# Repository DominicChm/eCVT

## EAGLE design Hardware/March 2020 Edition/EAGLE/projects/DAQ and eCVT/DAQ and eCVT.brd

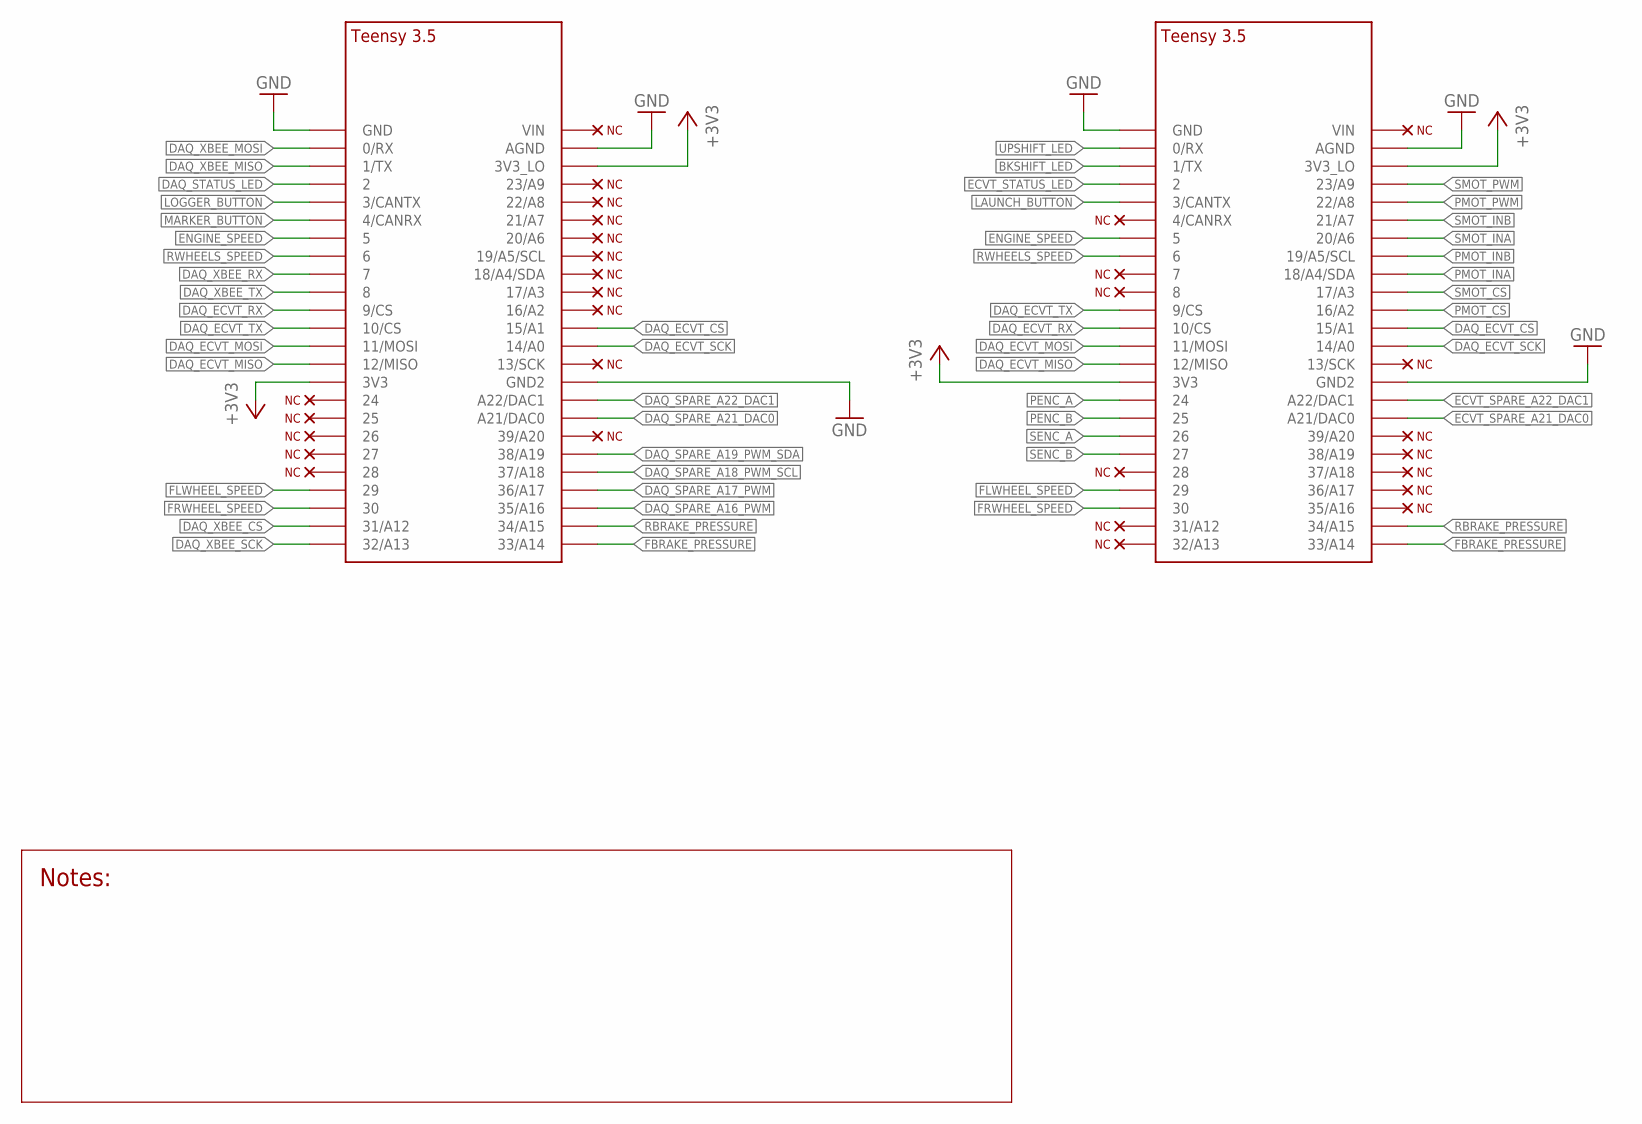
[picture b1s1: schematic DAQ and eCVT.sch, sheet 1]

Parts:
U$31, U$33: TEENSY_3.5_BAJA

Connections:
+3V3: U$31.3V3, U$31.3V3_LO, U$33.3V3, U$33.3V3_LO; also elsewhere on the board
BKSHIFT_LED: U$33.1/TX; also elsewhere on the board
DAQ_ECVT_CS: U$31.15/A1, U$33.15/A1
DAQ_ECVT_MISO: U$31.12/MISO, U$33.12/MISO
DAQ_ECVT_MOSI: U$31.11/MOSI, U$33.11/MOSI
DAQ_ECVT_RX: U$31.9/CS, U$33.10/CS
DAQ_ECVT_SCK: U$31.14/A0, U$33.14/A0
DAQ_ECVT_TX: U$31.10/CS, U$33.9/CS
DAQ_SPARE_A16_PWM: U$31.35/A16; also elsewhere on the board
DAQ_SPARE_A17_PWM: U$31.36/A17; also elsewhere on the board
DAQ_SPARE_A18_PWM_SCL: U$31.37/A18; also elsewhere on the board
DAQ_SPARE_A19_PWM_SDA: U$31.38/A19; also elsewhere on the board
DAQ_SPARE_A21_DAC0: U$31.21/DAC0 (A21/DAC0); also elsewhere on the board
DAQ_SPARE_A22_DAC1: U$31.A22/DAC1; also elsewhere on the board
DAQ_STATUS_LED: U$31.2; also elsewhere on the board
DAQ_XBEE_CS: U$31.31/A12; also elsewhere on the board
DAQ_XBEE_MISO: U$31.1/TX; also elsewhere on the board
DAQ_XBEE_MOSI: U$31.0/RX; also elsewhere on the board
DAQ_XBEE_RX: U$31.7; also elsewhere on the board
DAQ_XBEE_SCK: U$31.32/A13; also elsewhere on the board
DAQ_XBEE_TX: U$31.8; also elsewhere on the board
ECVT_SPARE_A21_DAC0: U$33.21/DAC0 (A21/DAC0); also elsewhere on the board
ECVT_SPARE_A22_DAC1: U$33.A22/DAC1; also elsewhere on the board
ECVT_STATUS_LED: U$33.2; also elsewhere on the board
ENGINE_SPEED: U$31.5, U$33.5; also elsewhere on the board
FBRAKE_PRESSURE: U$31.33/A14, U$33.33/A14; also elsewhere on the board
FLWHEEL_SPEED: U$31.29, U$33.29; also elsewhere on the board
FRWHEEL_SPEED: U$31.30, U$33.30; also elsewhere on the board
GND: U$31.AGND, U$31.GND, U$31.GND2, U$33.AGND, U$33.GND, U$33.GND2; also elsewhere on the board
LAUNCH_BUTTON: U$33.3/CANTX; also elsewhere on the board
LOGGER_BUTTON: U$31.3/CANTX; also elsewhere on the board
MARKER_BUTTON: U$31.4/CANRX; also elsewhere on the board
PENC_A: U$33.24; also elsewhere on the board
PENC_B: U$33.25; also elsewhere on the board
PMOT_CS: U$33.16/A2; also elsewhere on the board
PMOT_INA: U$33.18/A4/SDA; also elsewhere on the board
PMOT_INB: U$33.19/A5/SCL; also elsewhere on the board
PMOT_PWM: U$33.22/A8; also elsewhere on the board
RBRAKE_PRESSURE: U$31.34/A15, U$33.34/A15; also elsewhere on the board
RWHEELS_SPEED: U$31.6, U$33.6; also elsewhere on the board
SENC_A: U$33.26; also elsewhere on the board
SENC_B: U$33.27; also elsewhere on the board
SMOT_CS: U$33.17/A3; also elsewhere on the board
SMOT_INA: U$33.20/A6; also elsewhere on the board
SMOT_INB: U$33.21/A7; also elsewhere on the board
SMOT_PWM: U$33.23/A9; also elsewhere on the board
UPSHIFT_LED: U$33.0/RX; also elsewhere on the board

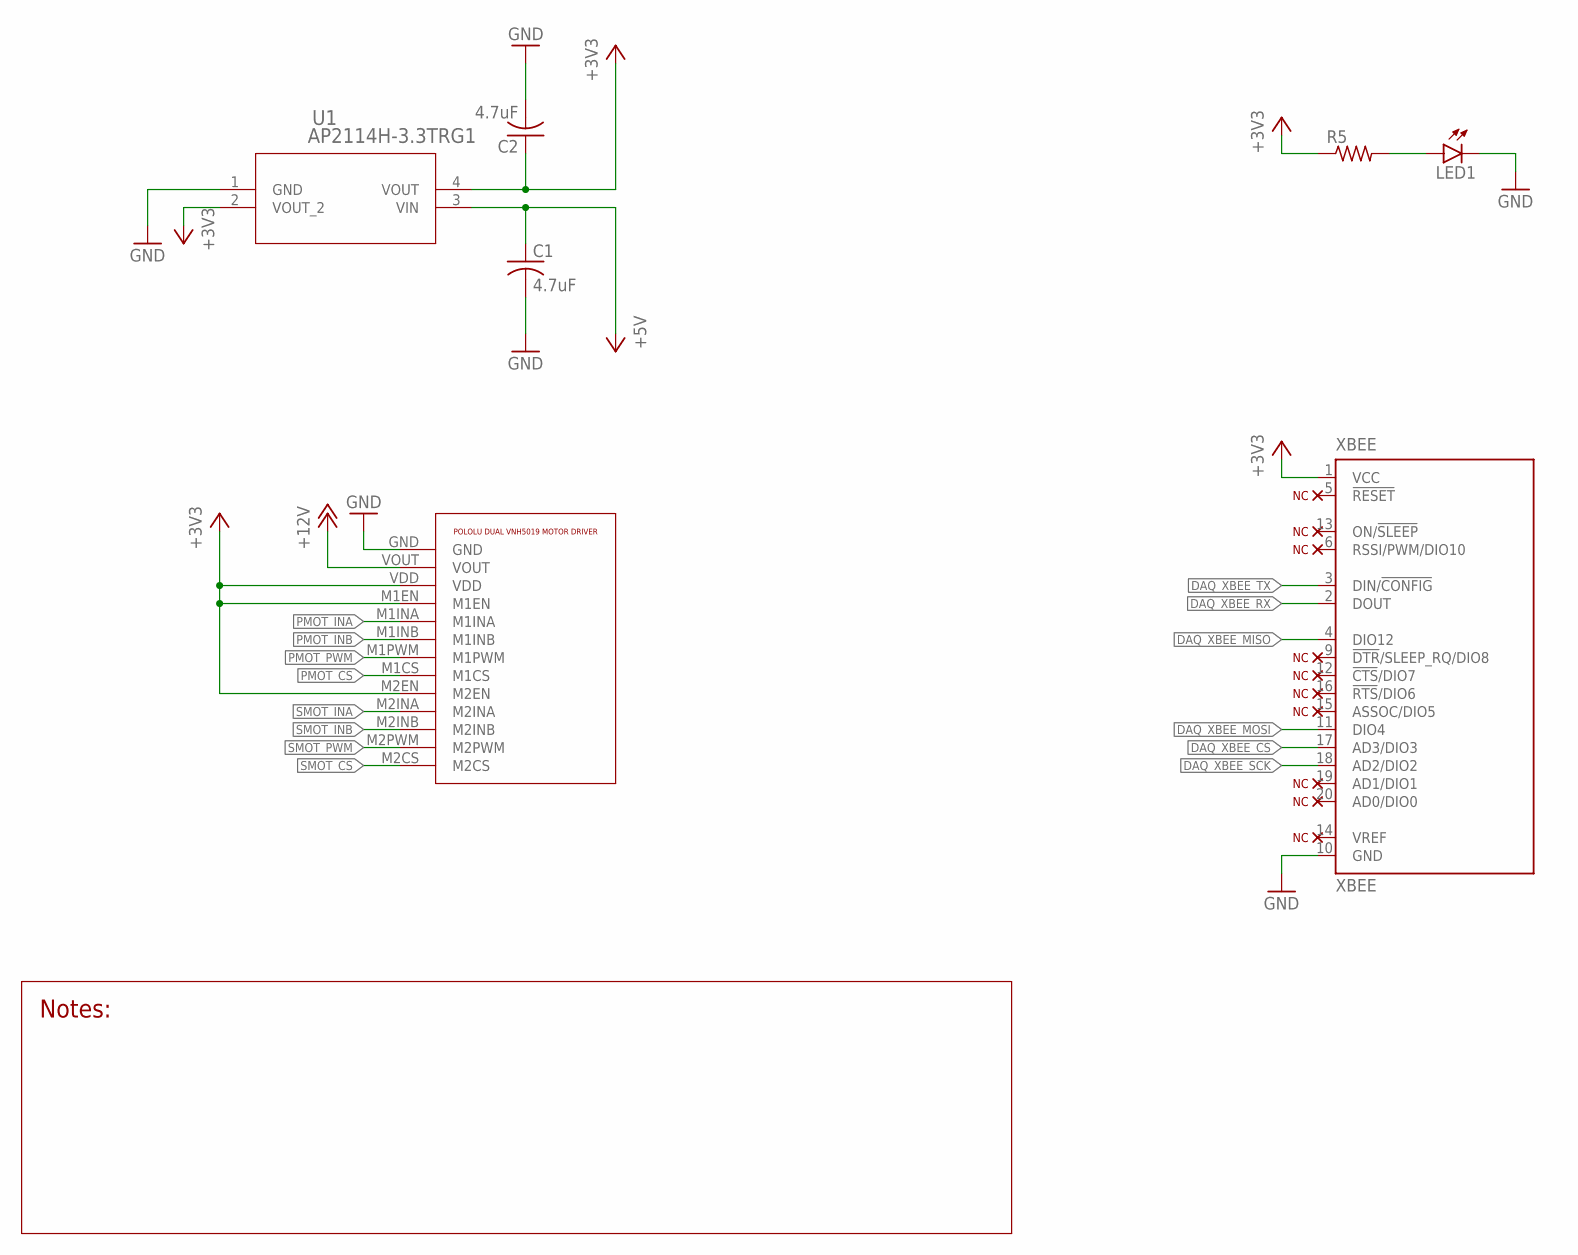
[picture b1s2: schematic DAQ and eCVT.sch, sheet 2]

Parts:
C1, C2: 4.7uF; C0805
LED1: LEDCHIPLED_0805; CHIPLED_0805
R5: R-US_R0805; R0805
U1: AP2114H-3.3TRG1; SOT-223
U$28: POLOLU_DUAL_VNH5019_BAJA
XBEE: XBEE

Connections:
+3V3: C2.1, R5.1, U1.2 (VOUT_2), U1.4 (VOUT), U$28.M1EN, U$28.M2EN, U$28.VDD, XBEE.1 (VCC); also elsewhere on the board
+5V: C1.1, U1.3 (VIN); also elsewhere on the board
+12V: U$28.VOUT; also elsewhere on the board
DAQ_XBEE_CS: XBEE.17 (AD3/DIO3); also elsewhere on the board
DAQ_XBEE_MISO: XBEE.4 (DIO12); also elsewhere on the board
DAQ_XBEE_MOSI: XBEE.11 (DIO4); also elsewhere on the board
DAQ_XBEE_RX: XBEE.2 (DOUT); also elsewhere on the board
DAQ_XBEE_SCK: XBEE.18 (AD2/DIO2); also elsewhere on the board
DAQ_XBEE_TX: XBEE.3 (DIN/!CONFIG); also elsewhere on the board
GND: C1.2, C2.2, LED1.C, U1.1 (GND), U$28.GND, XBEE.10 (GND); also elsewhere on the board
LED: LED1.A, R5.2
PMOT_CS: U$28.M1CS; also elsewhere on the board
PMOT_INA: U$28.M1INA; also elsewhere on the board
PMOT_INB: U$28.M1INB; also elsewhere on the board
PMOT_PWM: U$28.M1PWM; also elsewhere on the board
SMOT_CS: U$28.M2CS; also elsewhere on the board
SMOT_INA: U$28.M2INA; also elsewhere on the board
SMOT_INB: U$28.M2INB; also elsewhere on the board
SMOT_PWM: U$28.M2PWM; also elsewhere on the board

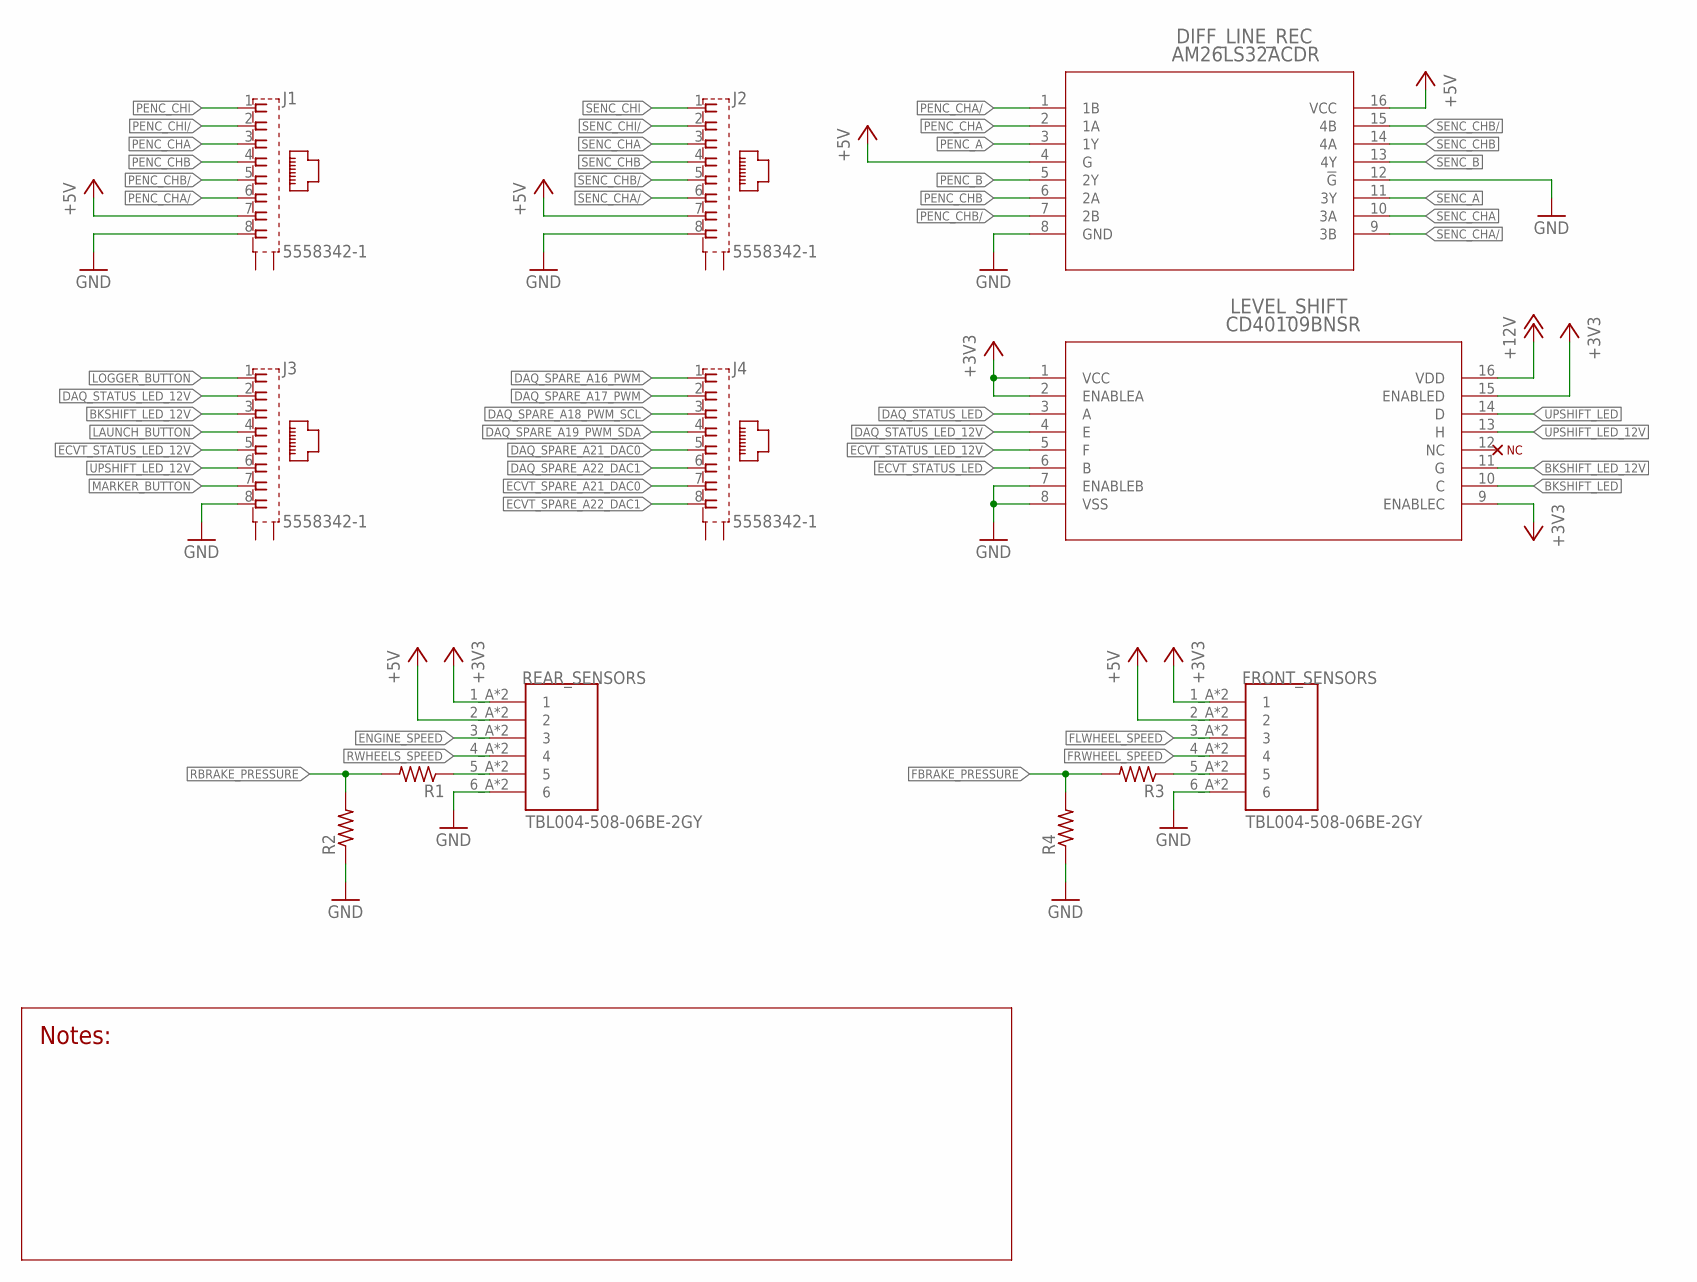
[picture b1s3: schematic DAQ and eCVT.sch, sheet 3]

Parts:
DIFF_LINE_REC: AM26LS32ACDR; D16
FRONT_SENSORS: TBL004-508-06BE-2GY; CUI_TBL004-508-06BE-2GY
J1, J2, J3, J4: 5558342-1; TE_5558342-1
LEVEL_SHIFT: CD40109BNSR; NS16
R1, R2, R3, R4: R-US_0204/7; 0204/7
REAR_SENSORS: TBL004-508-06BE-2GY; CUI_TBL004-508-06BE-2GY

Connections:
+3V3: FRONT_SENSORS.1_A (1), FRONT_SENSORS.1_B (1), LEVEL_SHIFT.1 (VCC), LEVEL_SHIFT.2 (ENABLEA), LEVEL_SHIFT.9 (ENABLEC), LEVEL_SHIFT.15 (ENABLED), REAR_SENSORS.1_A (1), REAR_SENSORS.1_B (1); also elsewhere on the board
+5V: DIFF_LINE_REC.4 (G), DIFF_LINE_REC.16 (VCC), FRONT_SENSORS.2_A (2), FRONT_SENSORS.2_B (2), J1.7, J2.7, REAR_SENSORS.2_A (2), REAR_SENSORS.2_B (2); also elsewhere on the board
+12V: LEVEL_SHIFT.16 (VDD); also elsewhere on the board
BKSHIFT_LED: LEVEL_SHIFT.10 (C); also elsewhere on the board
BKSHIFT_LED_12V: J3.3, LEVEL_SHIFT.11 (G)
DAQ_SPARE_A16_PWM: J4.1; also elsewhere on the board
DAQ_SPARE_A17_PWM: J4.2; also elsewhere on the board
DAQ_SPARE_A18_PWM_SCL: J4.3; also elsewhere on the board
DAQ_SPARE_A19_PWM_SDA: J4.4; also elsewhere on the board
DAQ_SPARE_A21_DAC0: J4.5; also elsewhere on the board
DAQ_SPARE_A22_DAC1: J4.6; also elsewhere on the board
DAQ_STATUS_LED: LEVEL_SHIFT.3 (A); also elsewhere on the board
DAQ_STATUS_LED_12V: J3.2, LEVEL_SHIFT.4 (E)
ECVT_SPARE_A21_DAC0: J4.7; also elsewhere on the board
ECVT_SPARE_A22_DAC1: J4.8; also elsewhere on the board
ECVT_STATUS_LED: LEVEL_SHIFT.6 (B); also elsewhere on the board
ECVT_STATUS_LED_12V: J3.5, LEVEL_SHIFT.5 (F)
ENGINE_SPEED: REAR_SENSORS.3_A (3), REAR_SENSORS.3_B (3); also elsewhere on the board
FBRAKE_PRESSURE: R3.2, R4.2; also elsewhere on the board
FBRAKE_PRESSURE_BEFORE_RESISTORS: FRONT_SENSORS.5_A (5), FRONT_SENSORS.5_B (5), R3.1
FLWHEEL_SPEED: FRONT_SENSORS.3_A (3), FRONT_SENSORS.3_B (3); also elsewhere on the board
FRWHEEL_SPEED: FRONT_SENSORS.4_A (4), FRONT_SENSORS.4_B (4); also elsewhere on the board
GND: DIFF_LINE_REC.8 (GND), DIFF_LINE_REC.12 (!G), FRONT_SENSORS.6_A (6), FRONT_SENSORS.6_B (6), J1.8, J2.8, J3.8, LEVEL_SHIFT.7 (ENABLEB), LEVEL_SHIFT.8 (VSS), R2.1, R4.1, REAR_SENSORS.6_A (6), REAR_SENSORS.6_B (6); also elsewhere on the board
LAUNCH_BUTTON: J3.4; also elsewhere on the board
LOGGER_BUTTON: J3.1; also elsewhere on the board
MARKER_BUTTON: J3.7; also elsewhere on the board
PENC_A: DIFF_LINE_REC.3 (1Y); also elsewhere on the board
PENC_B: DIFF_LINE_REC.5 (2Y); also elsewhere on the board
PENC_CHA: DIFF_LINE_REC.2 (1A), J1.3
PENC_CHA/: DIFF_LINE_REC.1 (1B), J1.6
PENC_CHB: DIFF_LINE_REC.6 (2A), J1.4
PENC_CHB/: DIFF_LINE_REC.7 (2B), J1.5
PENC_CHI: J1.1
PENC_CHI/: J1.2
RBRAKE_PRESSURE: R1.2, R2.2; also elsewhere on the board
RBRAKE_PRESSURE_BEFORE_RESISTORS: R1.1, REAR_SENSORS.5_A (5), REAR_SENSORS.5_B (5)
RWHEELS_SPEED: REAR_SENSORS.4_A (4), REAR_SENSORS.4_B (4); also elsewhere on the board
SENC_A: DIFF_LINE_REC.11 (3Y); also elsewhere on the board
SENC_B: DIFF_LINE_REC.13 (4Y); also elsewhere on the board
SENC_CHA: DIFF_LINE_REC.10 (3A), J2.3
SENC_CHA/: DIFF_LINE_REC.9 (3B), J2.6
SENC_CHB: DIFF_LINE_REC.14 (4A), J2.4
SENC_CHB/: DIFF_LINE_REC.15 (4B), J2.5
SENC_CHI: J2.1
SENC_CHI/: J2.2
UPSHIFT_LED: LEVEL_SHIFT.14 (D); also elsewhere on the board
UPSHIFT_LED_12V: J3.6, LEVEL_SHIFT.13 (H)

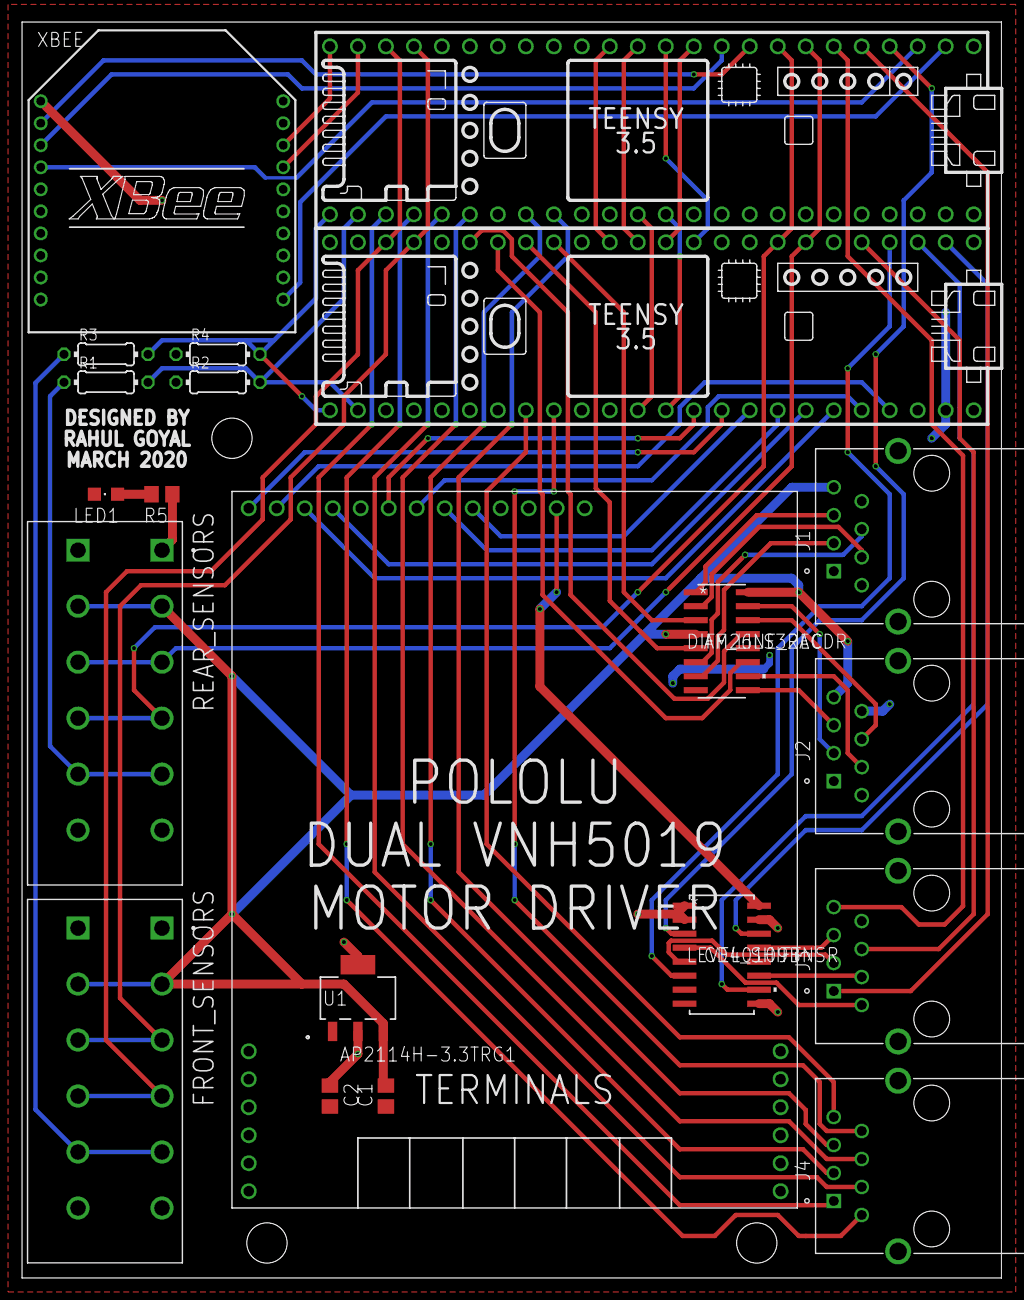
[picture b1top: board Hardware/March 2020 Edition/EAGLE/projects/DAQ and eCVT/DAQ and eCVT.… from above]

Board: 2 copper layers, 88.9 x 114.0 mm, 21 parts (0 on the bottom side), 64 nets.

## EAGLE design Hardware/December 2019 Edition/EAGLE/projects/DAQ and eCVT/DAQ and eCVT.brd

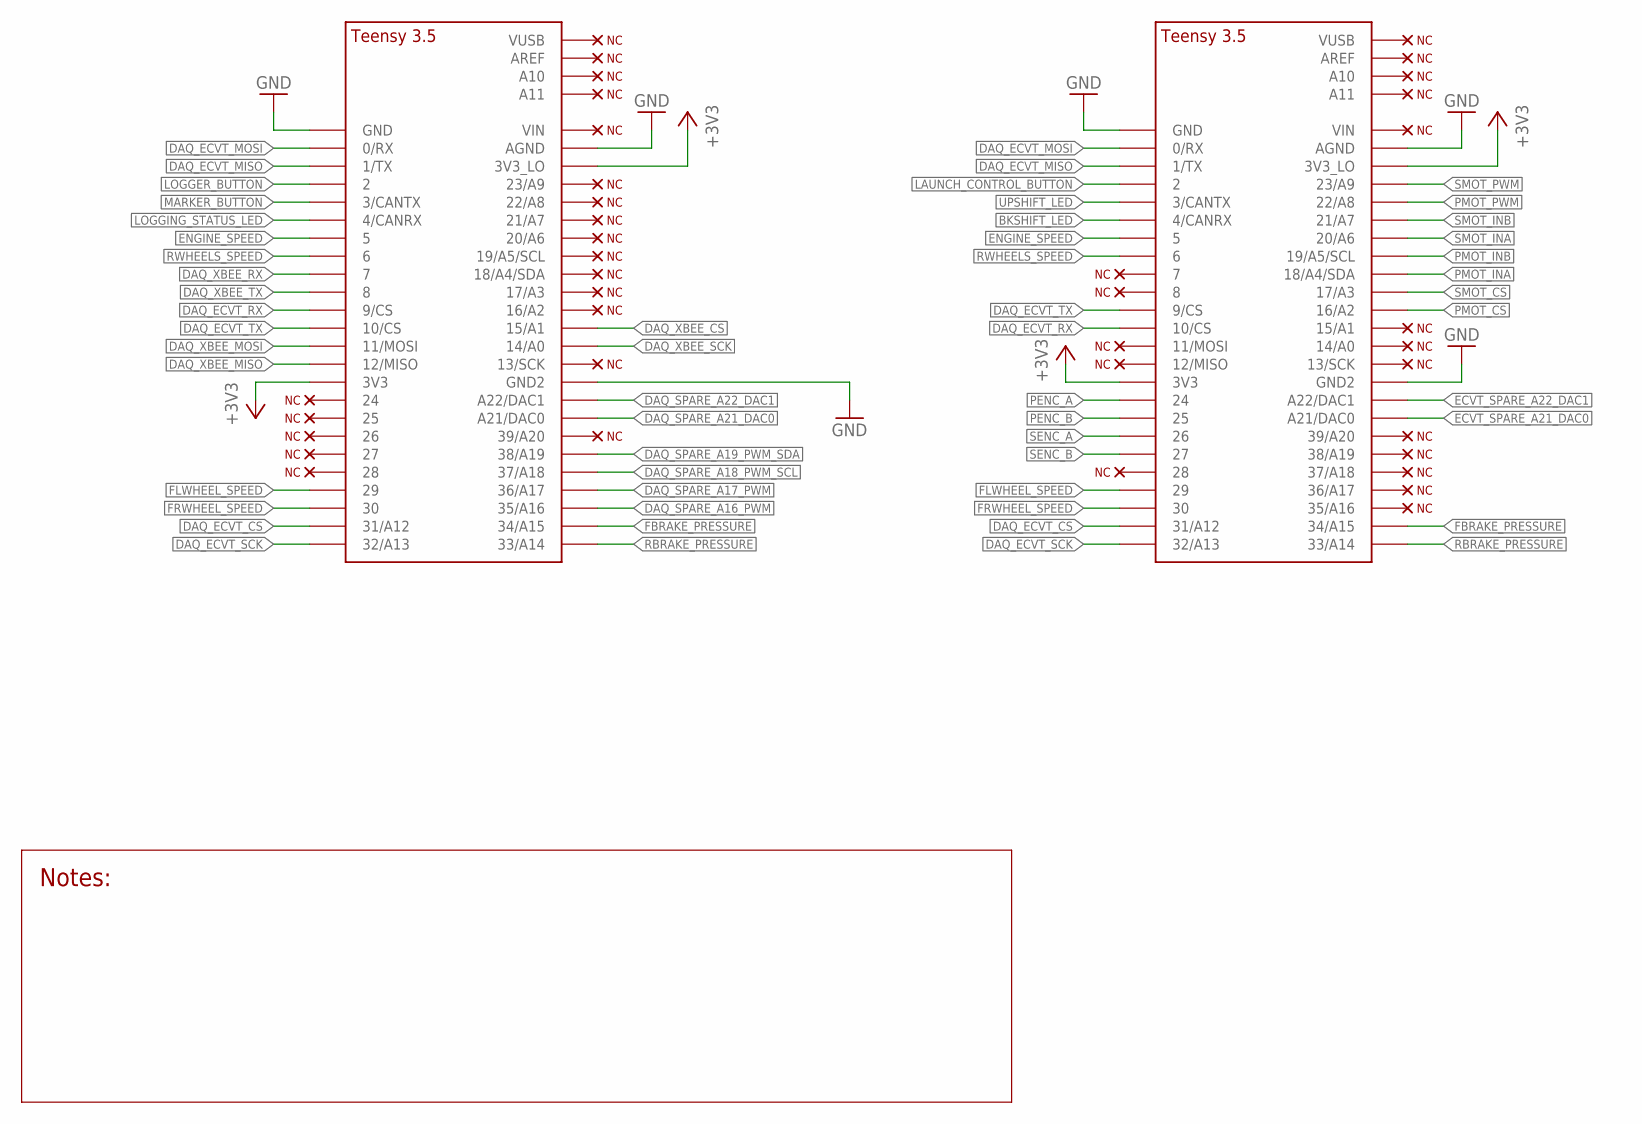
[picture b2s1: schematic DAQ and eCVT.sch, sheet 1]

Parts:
DAQ: TEENSY_3.5
ECVT: TEENSY_3.5

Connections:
+3V3: DAQ.3V3, DAQ.3V3_LO, ECVT.3V3, ECVT.3V3_LO; also elsewhere on the board
BKSHIFT_LED: ECVT.4/CANRX; also elsewhere on the board
DAQ_ECVT_CS: DAQ.31/A12, ECVT.31/A12
DAQ_ECVT_MISO: DAQ.1/TX, ECVT.1/TX
DAQ_ECVT_MOSI: DAQ.0/RX, ECVT.0/RX
DAQ_ECVT_RX: DAQ.9/CS, ECVT.10/CS
DAQ_ECVT_SCK: DAQ.32/A13, ECVT.32/A13
DAQ_ECVT_TX: DAQ.10/CS, ECVT.9/CS
DAQ_SPARE_A16_PWM: DAQ.35/A16; also elsewhere on the board
DAQ_SPARE_A17_PWM: DAQ.36/A17; also elsewhere on the board
DAQ_SPARE_A18_PWM_SCL: DAQ.37/A18; also elsewhere on the board
DAQ_SPARE_A19_PWM_SDA: DAQ.38/A19; also elsewhere on the board
DAQ_SPARE_A21_DAC0: DAQ.21/DAC0 (A21/DAC0); also elsewhere on the board
DAQ_SPARE_A22_DAC1: DAQ.A22/DAC1; also elsewhere on the board
DAQ_XBEE_CS: DAQ.15/A1; also elsewhere on the board
DAQ_XBEE_MISO: DAQ.12/MISO; also elsewhere on the board
DAQ_XBEE_MOSI: DAQ.11/MOSI; also elsewhere on the board
DAQ_XBEE_RX: DAQ.7; also elsewhere on the board
DAQ_XBEE_SCK: DAQ.14/A0; also elsewhere on the board
DAQ_XBEE_TX: DAQ.8; also elsewhere on the board
ECVT_SPARE_A21_DAC0: ECVT.21/DAC0 (A21/DAC0); also elsewhere on the board
ECVT_SPARE_A22_DAC1: ECVT.A22/DAC1; also elsewhere on the board
ENGINE_SPEED: DAQ.5, ECVT.5; also elsewhere on the board
FBRAKE_PRESSURE: DAQ.34/A15, ECVT.34/A15; also elsewhere on the board
FLWHEEL_SPEED: DAQ.29, ECVT.29; also elsewhere on the board
FRWHEEL_SPEED: DAQ.30, ECVT.30; also elsewhere on the board
GND: DAQ.AGND, DAQ.GND, DAQ.GND2, ECVT.AGND, ECVT.GND, ECVT.GND2; also elsewhere on the board
LAUNCH_CONTROL_BUTTON: ECVT.2; also elsewhere on the board
LOGGER_BUTTON: DAQ.2; also elsewhere on the board
LOGGING_STATUS_LED: DAQ.4/CANRX; also elsewhere on the board
MARKER_BUTTON: DAQ.3/CANTX; also elsewhere on the board
PENC_A: ECVT.24; also elsewhere on the board
PENC_B: ECVT.25; also elsewhere on the board
PMOT_CS: ECVT.16/A2; also elsewhere on the board
PMOT_INA: ECVT.18/A4/SDA; also elsewhere on the board
PMOT_INB: ECVT.19/A5/SCL; also elsewhere on the board
PMOT_PWM: ECVT.22/A8; also elsewhere on the board
RBRAKE_PRESSURE: DAQ.33/A14, ECVT.33/A14; also elsewhere on the board
RWHEELS_SPEED: DAQ.6, ECVT.6; also elsewhere on the board
SENC_A: ECVT.26; also elsewhere on the board
SENC_B: ECVT.27; also elsewhere on the board
SMOT_CS: ECVT.17/A3; also elsewhere on the board
SMOT_INA: ECVT.20/A6; also elsewhere on the board
SMOT_INB: ECVT.21/A7; also elsewhere on the board
SMOT_PWM: ECVT.23/A9; also elsewhere on the board
UPSHIFT_LED: ECVT.3/CANTX; also elsewhere on the board

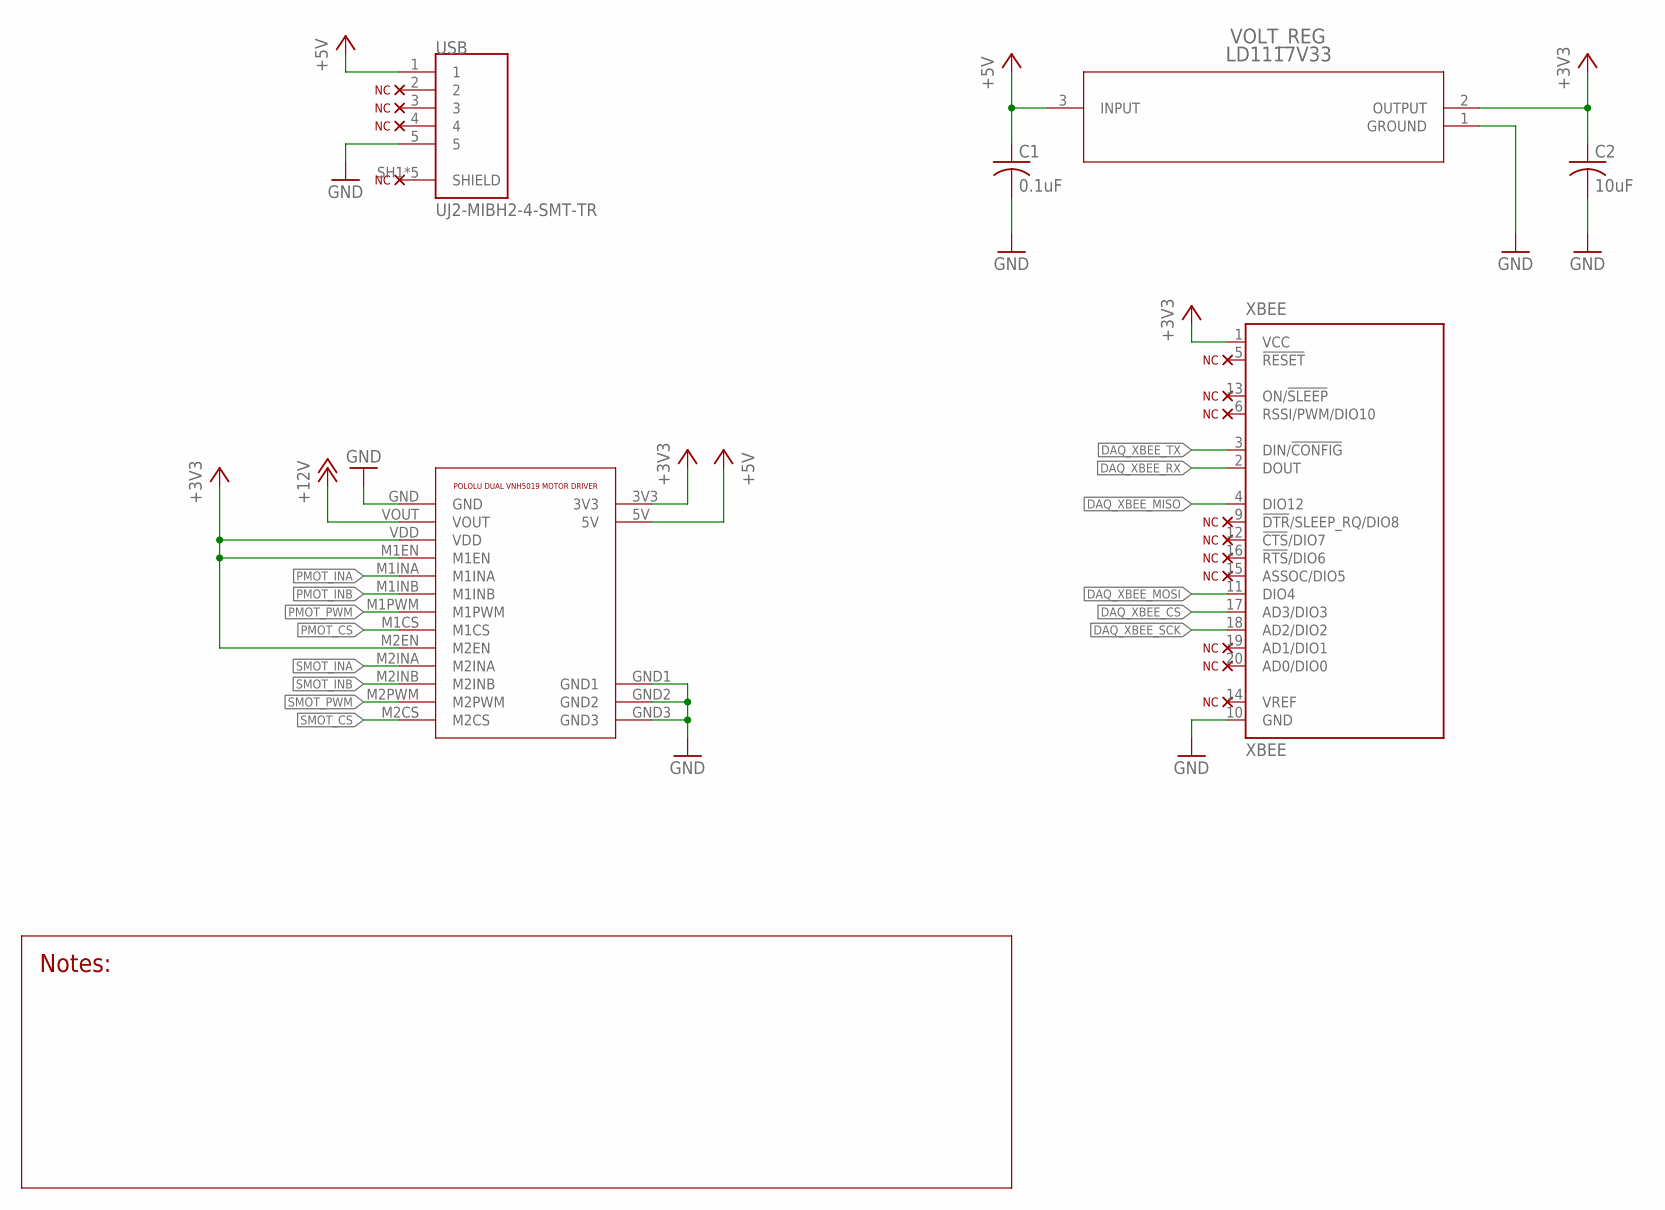
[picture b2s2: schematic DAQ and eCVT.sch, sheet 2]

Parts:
C1: 0.1uF; C0805
C2: 10uF; C0805
MOTOR_DRIVER: POLOLU_DUAL_VNH5019
USB: UJ2-MIBH2-4-SMT-TR; CUI_UJ2-MIBH2-4-SMT-TR
VOLT_REG: LD1117V33; TO-220
XBEE: XBEE

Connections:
+3V3: C2.1, MOTOR_DRIVER.3V3, MOTOR_DRIVER.M1EN, MOTOR_DRIVER.M2EN, MOTOR_DRIVER.VDD, VOLT_REG.2 (OUTPUT), XBEE.1 (VCC); also elsewhere on the board
+5V: C1.1, MOTOR_DRIVER.5V, USB.1, VOLT_REG.3 (INPUT); also elsewhere on the board
+12V: MOTOR_DRIVER.VOUT; also elsewhere on the board
DAQ_XBEE_CS: XBEE.17 (AD3/DIO3); also elsewhere on the board
DAQ_XBEE_MISO: XBEE.4 (DIO12); also elsewhere on the board
DAQ_XBEE_MOSI: XBEE.11 (DIO4); also elsewhere on the board
DAQ_XBEE_RX: XBEE.2 (DOUT); also elsewhere on the board
DAQ_XBEE_SCK: XBEE.18 (AD2/DIO2); also elsewhere on the board
DAQ_XBEE_TX: XBEE.3 (DIN/!CONFIG); also elsewhere on the board
GND: C1.2, C2.2, MOTOR_DRIVER.GND, MOTOR_DRIVER.GND1, MOTOR_DRIVER.GND2, MOTOR_DRIVER.GND3, USB.5, VOLT_REG.1 (GROUND), XBEE.10 (GND); also elsewhere on the board
unnamed: USB.SH1 (SHIELD), USB.SH2 (SHIELD), USB.SH3 (SHIELD), USB.SH4 (SHIELD), USB.SH5 (SHIELD)
PMOT_CS: MOTOR_DRIVER.M1CS; also elsewhere on the board
PMOT_INA: MOTOR_DRIVER.M1INA; also elsewhere on the board
PMOT_INB: MOTOR_DRIVER.M1INB; also elsewhere on the board
PMOT_PWM: MOTOR_DRIVER.M1PWM; also elsewhere on the board
SMOT_CS: MOTOR_DRIVER.M2CS; also elsewhere on the board
SMOT_INA: MOTOR_DRIVER.M2INA; also elsewhere on the board
SMOT_INB: MOTOR_DRIVER.M2INB; also elsewhere on the board
SMOT_PWM: MOTOR_DRIVER.M2PWM; also elsewhere on the board

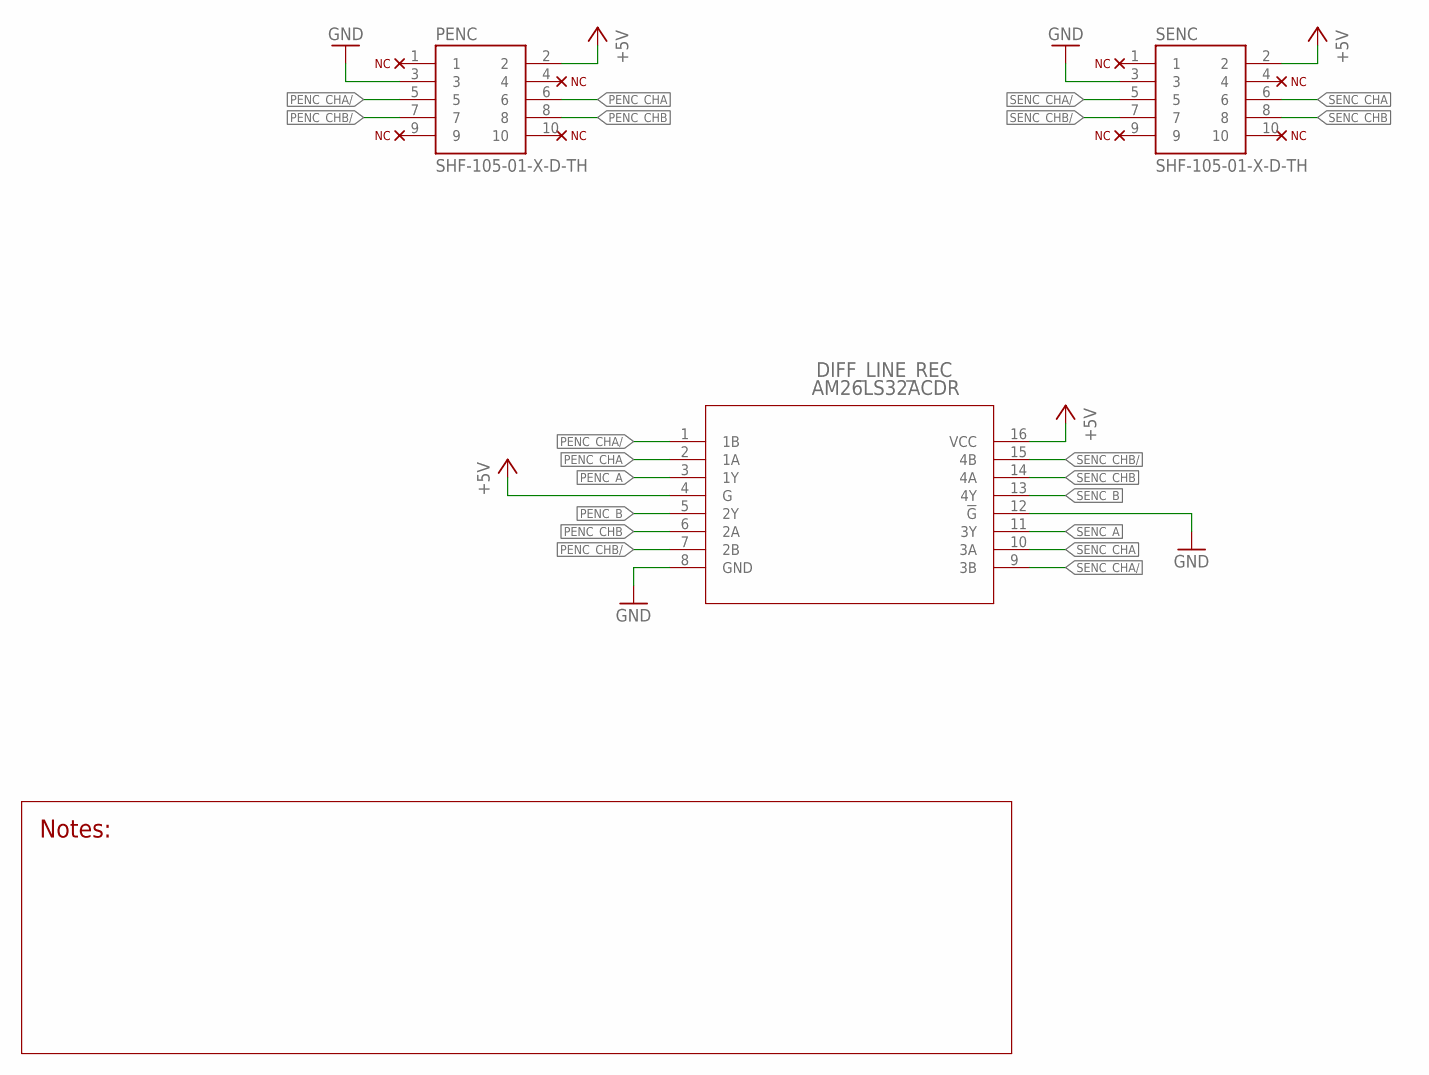
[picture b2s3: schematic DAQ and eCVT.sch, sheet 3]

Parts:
DIFF_LINE_REC: AM26LS32ACDR; D16
PENC: SHF-105-01-X-D-TH
SENC: SHF-105-01-X-D-TH

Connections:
+5V: DIFF_LINE_REC.4 (G), DIFF_LINE_REC.16 (VCC), PENC.2, SENC.2; also elsewhere on the board
GND: DIFF_LINE_REC.8 (GND), DIFF_LINE_REC.12 (!G), PENC.3, SENC.3; also elsewhere on the board
PENC_A: DIFF_LINE_REC.3 (1Y); also elsewhere on the board
PENC_B: DIFF_LINE_REC.5 (2Y); also elsewhere on the board
PENC_CHA: DIFF_LINE_REC.2 (1A), PENC.6
PENC_CHA/: DIFF_LINE_REC.1 (1B), PENC.5
PENC_CHB: DIFF_LINE_REC.6 (2A), PENC.8
PENC_CHB/: DIFF_LINE_REC.7 (2B), PENC.7
SENC_A: DIFF_LINE_REC.11 (3Y); also elsewhere on the board
SENC_B: DIFF_LINE_REC.13 (4Y); also elsewhere on the board
SENC_CHA: DIFF_LINE_REC.10 (3A), SENC.6
SENC_CHA/: DIFF_LINE_REC.9 (3B), SENC.5
SENC_CHB: DIFF_LINE_REC.14 (4A), SENC.8
SENC_CHB/: DIFF_LINE_REC.15 (4B), SENC.7
